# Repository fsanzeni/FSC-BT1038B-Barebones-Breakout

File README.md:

# FSC-BT1038B Breakout Board

_A breakout board designed using KiCad. AIM: test out Auracast protocols to (eventually) build a Bluetooth speaker_

## Overview

This repository contains the design files for a custom breakout board created in KiCad. The board is intended for evaluating the [Feasycom FSC-BT1038B module](https://www.feasycom.com/fsc-bt1038b). All pins are broken out and grouped for your convenience.

## Features

-   **Modern IC:** board based on the [QCC3084](https://www.qualcomm.com/products/internet-of-things/consumer/audio/qcc30xx-series/qcc3084) IC by Qualcomm.
-   **(Relatively) Compact Design:** ~60x45mm
-   **Voltage Compatibility:** it accepts 5v USB, stepped to 3.3v via an AMS1117. The FSC-BT1038B offers additional 1.8v out (TP1) and 3.3v out (~50mA max, TP2).
-   **Pinout:** all pins are broken out and labeled on the silkscreen. 
-   **Additional Features:** three status LEDs connected to the LED0, LED1 and LED2 pins. Three user buttons are also present on the board (see silkscreen labelling).

## Schematic

## Checklist

### 🛠️ Project Status

| Component | Status |
| -------- | ------- |
| Schematic | ✅ Done |
| PCB Layout | ✅ Done |
| Gerber Files | ✅ Generated |
| Fabrication | ✅ Done |
| Assembly | ✅ Done |
| Testing | ✅ Done |
| Firmware | 🔄 In Progress |
| Documentation | 🔄 In Progress |

Please note - the board has been tested and functions as intended.

## Getting Started

### Prerequisites

Ensure you have the following installed:

- [KiCad](https://www.kicad.org/) (version 8.0 or later)
- Add the custom libraries to your (local) project. They're included in this repo in the hardware/libraries/ folder

## Files & Directory Structure

```
📂 kicad-breakout/
 ├── 📂 documentation/			# Documentation (WIP) - find in here the schematic (pdf, svg and jpg)
 ├── 📂 firmware/				# Firmware
 ├── 📂 hardware/				# KiCad design files
 	├── 📂 bom/					# Interactive BOM (html)
 	├── 📂 fabrication/			# Fabrication files
 	├── 📂 libraries/			# Please don't forget to include these!
```

## Contribution

Contributions are welcome! Feel free to submit a pull request or open an issue for discussion.

## License

This project is licensed under the [CERN-OHL-S v2](https://ohwr.org/cern_ohl_s_v2.txt).

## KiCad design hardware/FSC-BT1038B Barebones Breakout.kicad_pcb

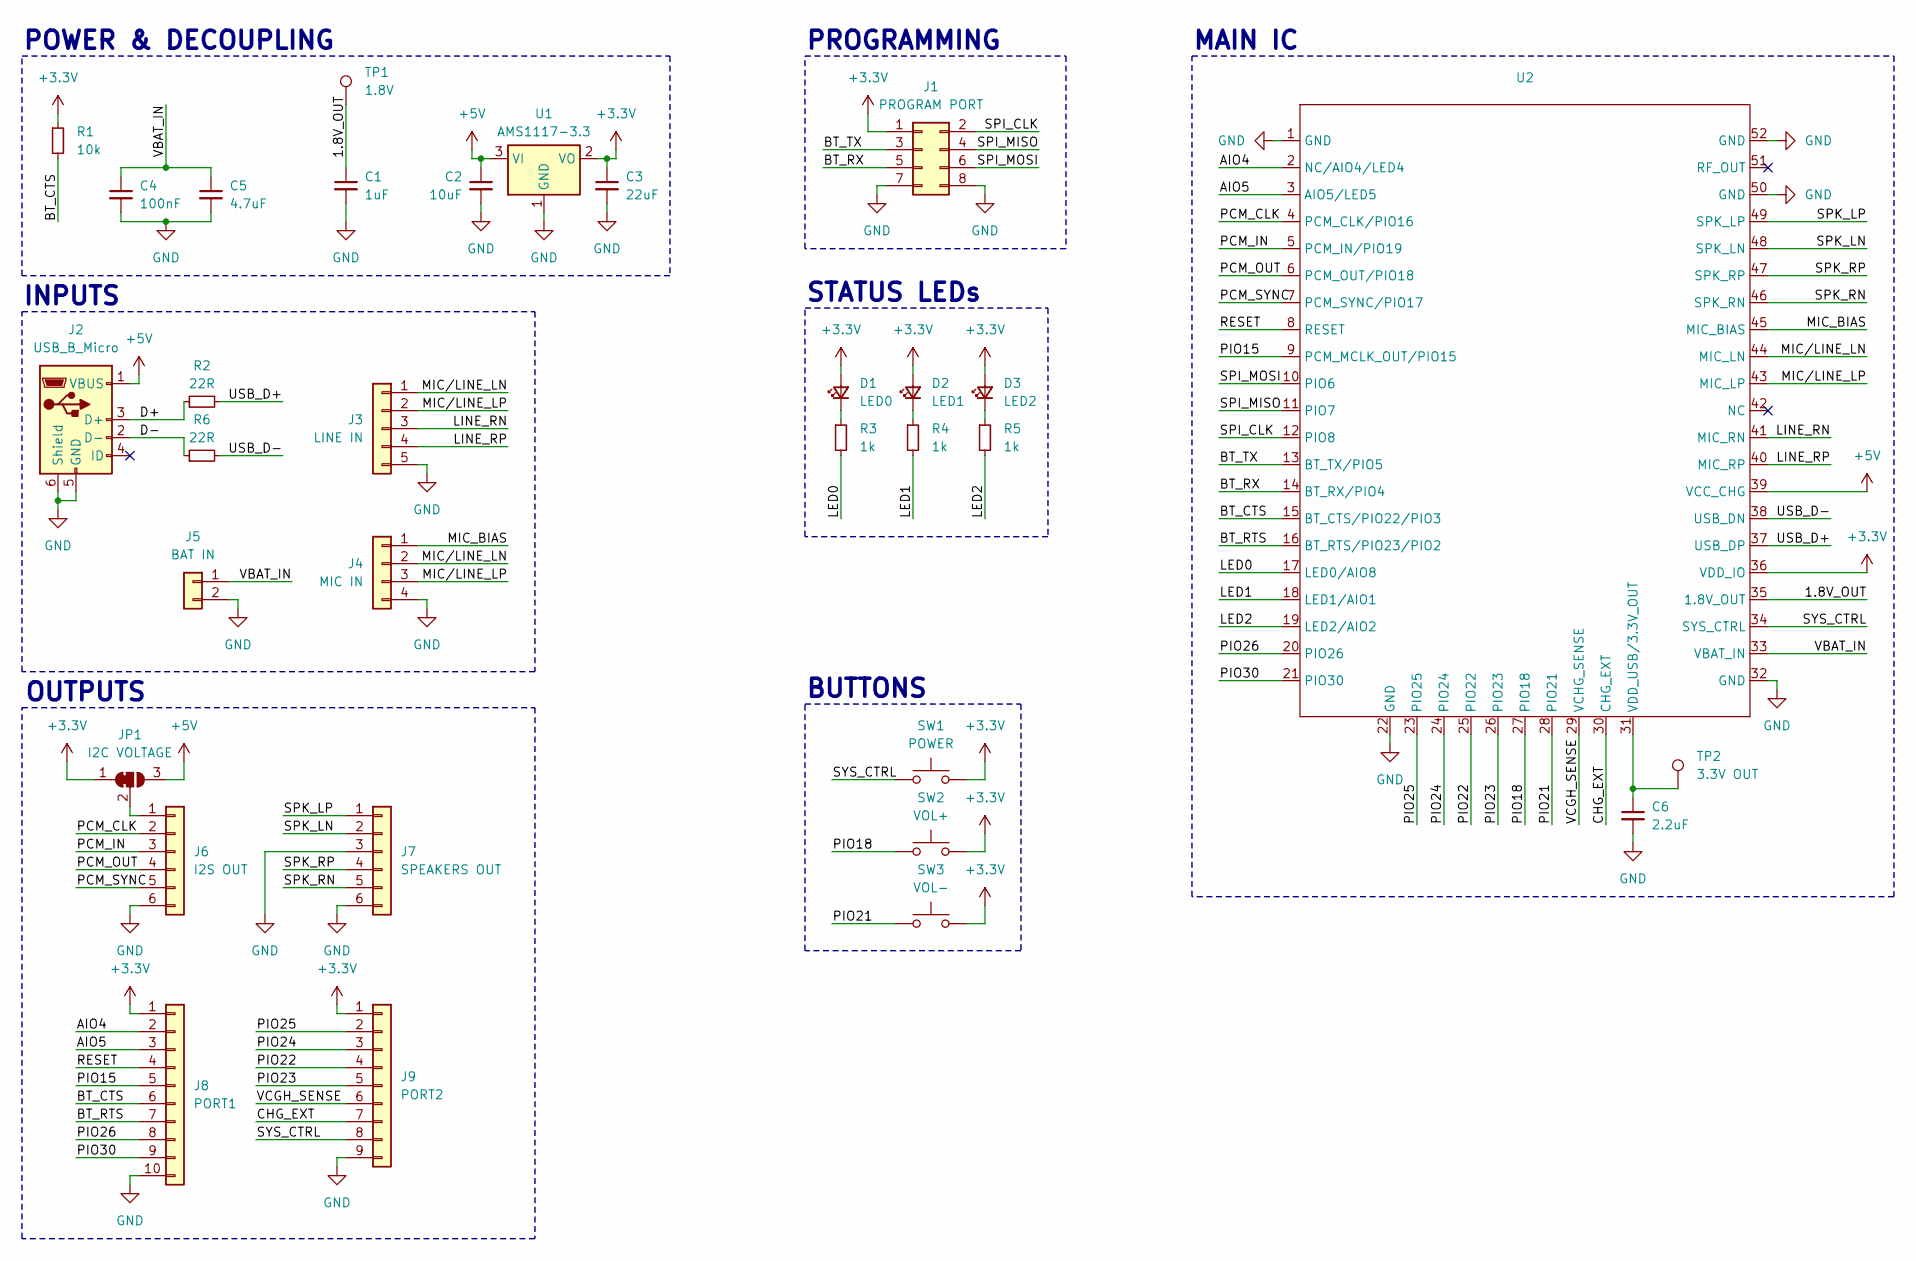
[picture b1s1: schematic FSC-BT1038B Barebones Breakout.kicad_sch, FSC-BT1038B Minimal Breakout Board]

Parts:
C1: 1uF; C_0603_1608Metric_Pad1.08x0.95mm_HandSolder
C2: 10uF; C_0603_1608Metric_Pad1.08x0.95mm_HandSolder
C3: 22uF; C_0603_1608Metric_Pad1.08x0.95mm_HandSolder
C4: 100nF; C_0603_1608Metric_Pad1.08x0.95mm_HandSolder
C5: 4.7uF; C_0603_1608Metric_Pad1.08x0.95mm_HandSolder
C6: 2.2uF; C_0603_1608Metric_Pad1.08x0.95mm_HandSolder
D1: LED0; LED_0603_1608Metric_Pad1.05x0.95mm_HandSolder
D2: LED1; LED_0603_1608Metric_Pad1.05x0.95mm_HandSolder
D3: LED2; LED_0603_1608Metric_Pad1.05x0.95mm_HandSolder
J1: PROGRAM PORT; PinSocket_2x04_P2.54mm_Vertical
J2: USB_B_Micro; KH-MICRO5P-JN
J3: LINE IN; PinSocket_1x05_P2.54mm_Vertical
J4: MIC IN; PinSocket_1x04_P2.54mm_Vertical
J5: BAT IN; PinSocket_1x02_P2.54mm_Vertical
J6: I2S OUT; PinSocket_1x06_P2.54mm_Vertical
J7: SPEAKERS OUT; PinSocket_1x06_P2.54mm_Vertical
J8: PORT1; PinSocket_1x10_P2.54mm_Vertical
J9: PORT2; PinSocket_1x09_P2.54mm_Vertical
JP1: I2C VOLTAGE; SolderJumper-3_P1.3mm_Bridged2Bar12_Pad1.0x1.5mm_NumberLabe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
R1: 10k; R_0603_1608Metric_Pad0.98x0.95mm_HandSolder
R2, R6: 22R; R_0603_1608Metric_Pad0.98x0.95mm_HandSolder
R3, R4, R5: 1k; R_0603_1608Metric_Pad0.98x0.95mm_HandSolder
SW1: POWER; TS3425BA
SW2: VOL+; TS3425BA
SW3: VOL-; TS3425BA
TP1: 1.8V; TestPoint_Pad_D1.5mm
TP2: 3.3V OUT; TestPoint_Pad_D1.5mm
U1: AMS1117-3.3; SOT-223-3_TabPin2
U2: FSC-BT1038B

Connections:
+3.3V: C3.1, D1.2 (A), D2.2 (A), D3.2 (A), J1.1, J8.1, J9.1, JP1.1 (A), R1.1, SW1.2, SW2.2, SW3.2, U1.2 (VO), U2.36 (VDD_IO)
+5V: C2.1, J2.1 (VBUS), JP1.3 (B), U1.3 (VI), U2.39 (VCC_CHG)
/1.8V_OUT: C1.1, TP1.1, U2.35 (1.8V_OUT)
/AIO4: J8.2, U2.2 (NC/AIO4/LED4)
/AIO5: J8.3, U2.3 (AIO5/LED5)
/BT_CTS: J8.6, R1.2, U2.15 (BT_CTS/PIO22/PIO3)
/BT_RTS: J8.7, U2.16 (BT_RTS/PIO23/PIO2)
/BT_RX: J1.5, U2.14 (BT_RX/PIO4)
/BT_TX: J1.3, U2.13 (BT_TX/PIO5)
/CHG_EXT: J9.7, U2.30 (CHG_EXT)
/D+: J2.3 (D+), R2.1
/D-: J2.2 (D-), R6.1
/LED0: R3.2, U2.17 (LED0/AIO8)
/LED1: R4.2, U2.18 (LED1/AIO1)
/LED2: R5.2, U2.19 (LED2/AIO2)
/LINE_RN: J3.3, U2.41 (MIC_RN)
/LINE_RP: J3.4, U2.40 (MIC_RP)
/MIC_BIAS: J4.1, U2.45 (MIC_BIAS)
/MIC/LINE_LN: J3.1, J4.2, U2.44 (MIC_LN)
/MIC/LINE_LP: J3.2, J4.3, U2.43 (MIC_LP)
/PCM_CLK: J6.2, U2.4 (PCM_CLK/PIO16)
/PCM_IN: J6.3, U2.5 (PCM_IN/PIO19)
/PCM_OUT: J6.4, U2.6 (PCM_OUT/PIO18)
/PCM_SYNC: J6.5, U2.7 (PCM_SYNC/PIO17)
/PIO15: J8.5, U2.9 (PCM_MCLK_OUT/PIO15)
/PIO18: SW2.1, U2.27 (PIO18)
/PIO21: SW3.1, U2.28 (PIO21)
/PIO22: J9.4, U2.25 (PIO22)
/PIO23: J9.5, U2.26 (PIO23)
/PIO24: J9.3, U2.24 (PIO24)
/PIO25: J9.2, U2.23 (PIO25)
/PIO26: J8.8, U2.20 (PIO26)
/PIO30: J8.9, U2.21 (PIO30)
/RESET: J8.4, U2.8 (RESET)
/SPI_CLK: J1.2, U2.12 (PIO8)
/SPI_MISO: J1.4, U2.11 (PIO7)
/SPI_MOSI: J1.6, U2.10 (PIO6)
/SPK_LN: J7.2, U2.48 (SPK_LN)
/SPK_LP: J7.1, U2.49 (SPK_LP)
/SPK_RN: J7.5, U2.46 (SPK_RN)
/SPK_RP: J7.4, U2.47 (SPK_RP)
/SYS_CTRL: J9.8, SW1.1, U2.34 (SYS_CTRL)
/USB_D+: R2.2, U2.37 (USB_DP)
/USB_D-: R6.2, U2.38 (USB_DN)
/VBAT_IN: C4.1, C5.1, J5.1, U2.33 (VBAT_IN)
/VCGH_SENSE: J9.6, U2.29 (VCHG_SENSE)
GND: C1.2, C2.2, C3.2, C4.2, C5.2, C6.2, J1.7, J1.8, J2.5 (GND), J2.6 (Shield), J3.5, J4.4, J5.2, J6.6, J7.3, J7.6, J8.10, J9.9, U1.1 (GND), U2.1 (GND), U2.22 (GND), U2.32 (GND), U2.50 (GND), U2.52 (GND)
unnamed: D1.1 (K), R3.1
unnamed: D2.1 (K), R4.1
unnamed: D3.1 (K), R5.1
unnamed: J6.1, JP1.2 (C)
unnamed: C6.1, TP2.1, U2.31 (VDD_USB/3.3V_OUT)

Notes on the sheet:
MAIN IC
POWER & DECOUPLING
INPUTS
OUTPUTS
STATUS LEDs
BUTTONS
PROGRAMMING

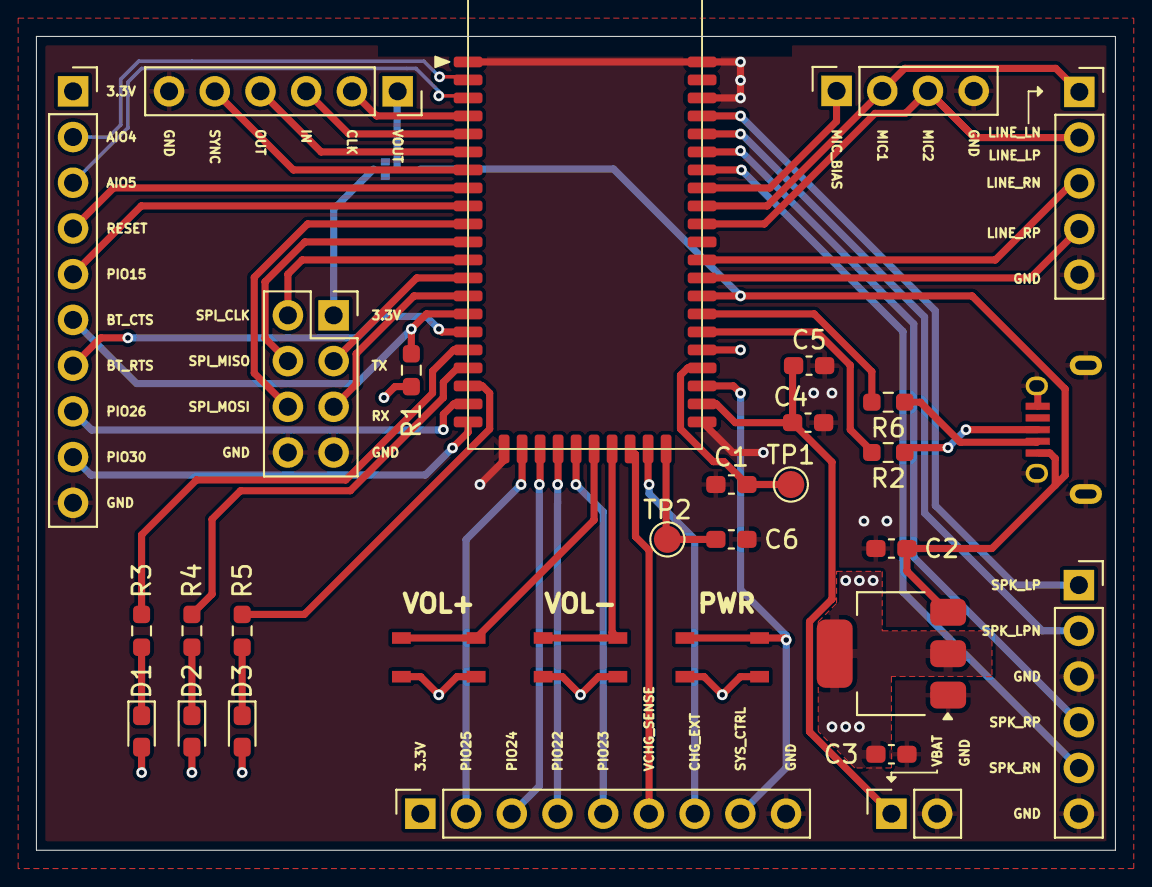
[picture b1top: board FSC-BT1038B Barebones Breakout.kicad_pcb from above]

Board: 4 copper layers, 59.9 x 45.2 mm, 32 parts (1 on the bottom side), 52 nets.

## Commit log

2025-02-03 Added schematics (pdf, svg & jpg). Edited README
2025-02-03 Fixed README
2025-02-03 Updated (again) README
2025-07-29 corrected schematic
